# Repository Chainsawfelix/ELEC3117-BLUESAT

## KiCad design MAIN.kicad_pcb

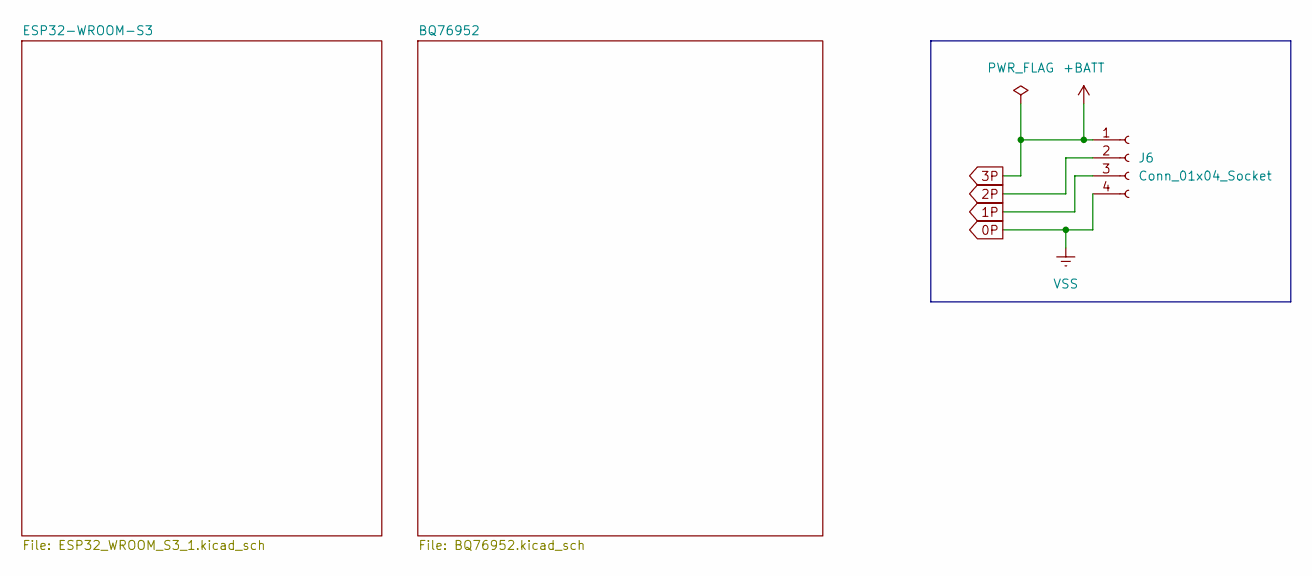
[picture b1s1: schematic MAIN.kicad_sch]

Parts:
J6: Conn_01x04_Socket; JST_XH_B4B-XH-A_1x04_P2.50mm_Vertical

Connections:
0P: J6.4; also elsewhere on the board
1P: J6.3; also elsewhere on the board
2P: J6.2; also elsewhere on the board

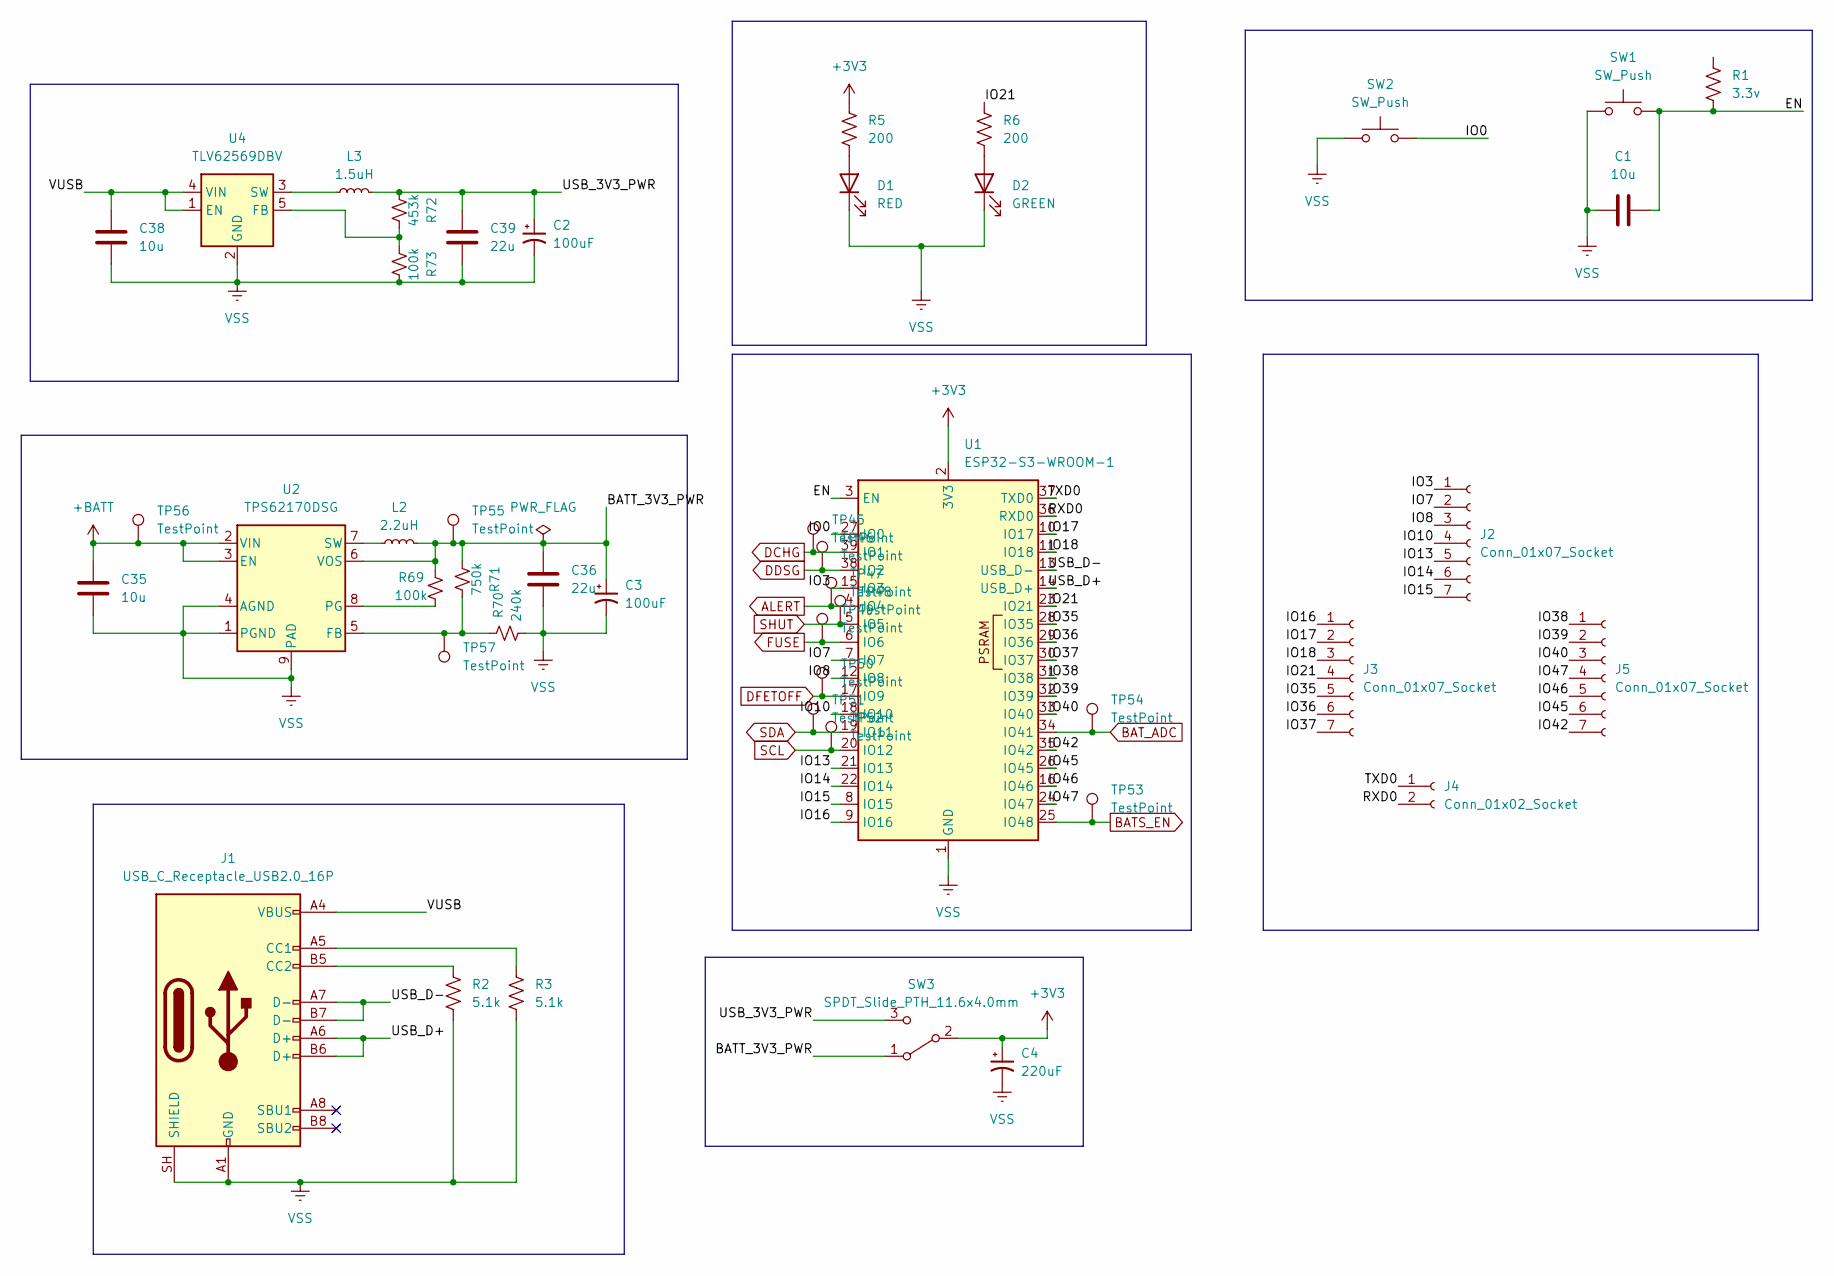
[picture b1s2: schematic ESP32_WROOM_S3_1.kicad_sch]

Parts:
C1, C35, C38: 10u; C_0805_2012Metric
C2, C3: 100uF; CP_Elec_6.3x5.8
C4: 220uF; CP_Elec_6.3x5.8
C36, C39: 22u; C_0805_2012Metric
D1: RED; LED_0805_2012Metric
D2: GREEN; LED_0805_2012Metric
J1: USB_C_Receptacle_USB2.0_16P; USB_C_Receptacle_GCT_USB4105-xx-A_16P_TopMnt_Horizontal
J2, J3, J5: Conn_01x07_Socket; JST_XH_B7B-XH-A_1x07_P2.50mm_Vertical
J4: Conn_01x02_Socket; JST_XH_B2B-XH-A_1x02_P2.50mm_Vertical
L2: 2.2uH; L_Wuerth_MAPI-3020
L3: 1.5uH; L_Wuerth_MAPI-3020
R1: 3.3v; R_0805_2012Metric
R2, R3: 5.1k; R_0805_2012Metric
R5, R6: 200; R_0805_2012Metric
R69, R73: 100k; R_0805_2012Metric
R70: 240k; R_0805_2012Metric
R71: 750k; R_0805_2012Metric
R72: 453k; R_0805_2012Metric
SW1, SW2: SW_Push; Push_SMD_4.2x3.2mm
SW3: SPDT_Slide_PTH_11.6x4.0mm; Slide_SPDT_PTH_11.6x4.0mm
TP45, TP46, TP47, TP48, TP49, TP50, TP51, TP52, TP53, TP54, TP55, TP56, TP57: TestPoint; TestPoint_Pad_D1.0mm
U1: ESP32-S3-WROOM-1
U2: TPS62170DSG; WSON-8-1EP_2x2mm_P0.5mm_EP0.9x1.6mm_ThermalVias
U4: TLV62569DBV; SOT-23-5

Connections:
0P: C1.1, C2.2, C3.2, C4.2, C35.2, C36.2, C38.2, C39.2, D1.1 (K), D2.1 (K), J1.A1 (GND), J1.A12 (GND), J1.B1 (GND), J1.B12 (GND), J1.SH (SHIELD), R2.2, R3.2, R70.2, R73.2, SW1.1, SW2.1, U1.1 (GND), U1.40 (GND), U1.41 (GND), U2.1 (PGND), U2.4 (AGND), U2.9 (PAD), U4.2 (GND); also elsewhere on the board
+3V3: C4.1, R5.1, SW3.2 (B), U1.2 (3V3); also elsewhere on the board
/ESP32-WROOM-S3/BATT_3V3_PWR: C3.1, C36.1, L2.2, R69.1, R71.1, SW3.1 (A), TP55.1 (1_1), U2.6 (VOS)
/ESP32-WROOM-S3/IO0: SW2.2, U1.27 (IO0)
/ESP32-WROOM-S3/IO3: J2.1, U1.15 (IO3)
/ESP32-WROOM-S3/IO7: J2.2, U1.7 (IO7)
/ESP32-WROOM-S3/IO8: J2.3, U1.12 (IO8)
/ESP32-WROOM-S3/IO10: J2.4, U1.18 (IO10)
/ESP32-WROOM-S3/IO13: J2.5, U1.21 (IO13)
/ESP32-WROOM-S3/IO14: J2.6, U1.22 (IO14)
/ESP32-WROOM-S3/IO15: J2.7, U1.8 (IO15)
/ESP32-WROOM-S3/IO16: J3.1, U1.9 (IO16)
/ESP32-WROOM-S3/IO17: J3.2, U1.10 (IO17)
/ESP32-WROOM-S3/IO18: J3.3, U1.11 (IO18)
/ESP32-WROOM-S3/IO21: J3.4, R6.1, U1.23 (IO21)
/ESP32-WROOM-S3/IO35: J3.5, U1.28 (IO35)
/ESP32-WROOM-S3/IO36: J3.6, U1.29 (IO36)
/ESP32-WROOM-S3/IO37: J3.7, U1.30 (IO37)
/ESP32-WROOM-S3/IO38: J5.1, U1.31 (IO38)
/ESP32-WROOM-S3/IO39: J5.2, U1.32 (IO39)
/ESP32-WROOM-S3/IO40: J5.3, U1.33 (IO40)
/ESP32-WROOM-S3/IO42: J5.7, U1.35 (IO42)
/ESP32-WROOM-S3/IO45: J5.6, U1.26 (IO45)
/ESP32-WROOM-S3/IO46: J5.5, U1.16 (IO46)
/ESP32-WROOM-S3/IO47: J5.4, U1.24 (IO47)
/ESP32-WROOM-S3/RXD0: J4.2, U1.36 (RXD0)
/ESP32-WROOM-S3/TXD0: J4.1, U1.37 (TXD0)
/ESP32-WROOM-S3/USB_3V3_PWR: C2.1, C39.1, L3.2, R72.1, SW3.3 (C)
/ESP32-WROOM-S3/USB_D+: J1.A6 (D+), J1.B6 (D+), U1.14 (USB_D+)
/ESP32-WROOM-S3/USB_D-: J1.A7 (D-), J1.B7 (D-), U1.13 (USB_D-)
/ESP32-WROOM-S3/VUSB: C38.1, J1.A4 (VBUS), J1.A9 (VBUS), J1.B4 (VBUS), J1.B9 (VBUS), U4.1 (EN), U4.4 (VIN)
ALERT: TP47.1, U1.4 (IO4); also elsewhere on the board
BATS_EN: TP53.1 (1_1), U1.25 (IO48); also elsewhere on the board
BAT_ADC: TP54.1 (1_1), U1.34 (IO41); also elsewhere on the board
DCHG: TP45.1, U1.39 (IO1); also elsewhere on the board
DDSG: TP46.1, U1.38 (IO2); also elsewhere on the board
DFETOFF: TP50.1, U1.17 (IO9); also elsewhere on the board
FUSE: TP49.1 (1_1), U1.6 (IO6); also elsewhere on the board
unnamed: D1.2 (A), R5.2
unnamed: D2.2 (A), R6.2
unnamed: J1.A5 (CC1), R3.1
unnamed: J1.B5 (CC2), R2.1
unnamed: R70.1, R71.2, TP57.1 (1_1), U2.5 (FB)
unnamed: R69.2, U2.8 (PG)
unnamed: L2.1, U2.7 (SW)
unnamed: R72.2, R73.1, U4.5 (FB)
unnamed: L3.1, U4.3 (SW)
SCL: TP52.1, U1.20 (IO12); also elsewhere on the board
SDA: TP51.1 (1_1), U1.19 (IO11); also elsewhere on the board
SHUT: TP48.1 (1_1), U1.5 (IO5); also elsewhere on the board

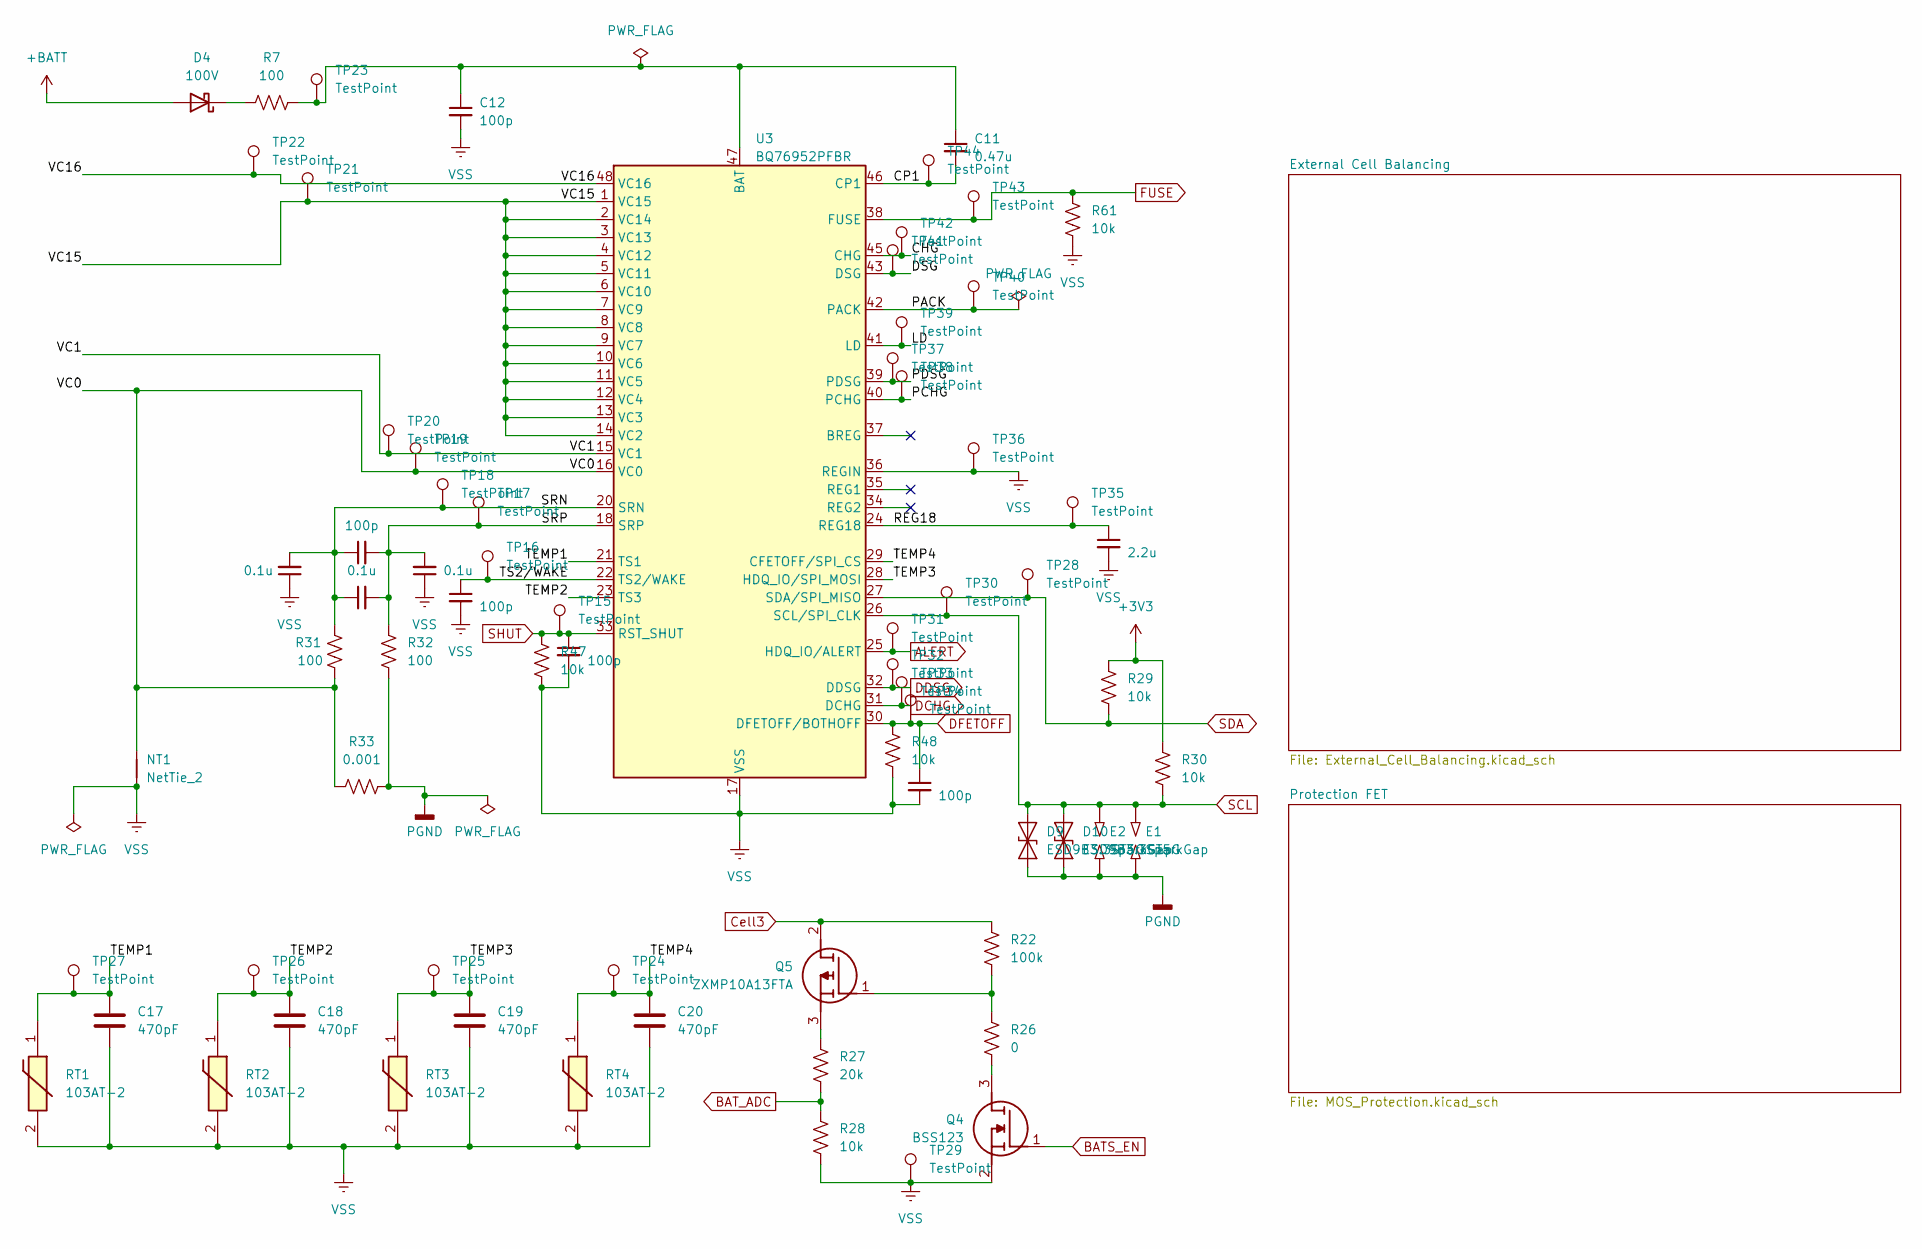
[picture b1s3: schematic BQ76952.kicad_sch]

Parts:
C11: 0.47u; C_0805_2012Metric
C12, C22, C30, C31, C32: 100p; C_0805_2012Metric
C17, C18, C19, C20: 470pF; C_0805_2012Metric
C21: 2.2u; C_0805_2012Metric
C23, C24, C25: 0.1u; C_0805_2012Metric
D4: 100V; D_0805_2012Metric
D9, D10: ESD9B3.3ST5G; D_SOD-923
E1, E2: SparkGap; SolderJumper-2_P1.3mm_Open_TrianglePad1.0x1.5mm
NT1: NetTie_2; SolderJumper-2_P1.3mm_Bridged2Bar_Pad1.0x1.5mm
Q4: BSS123; SOT96P237X111-3N; Mouser Part Number 512-BSS123
Q5: ZXMP10A13FTA; SOT96P240X110-3N; Mouser Part Number 522-ZXMP10A13FTA
R7, R31, R32: 100; R_0805_2012Metric
R22: 100k; R_0805_2012Metric
R26: 0; R_0805_2012Metric
R27: 20k; R_0805_2012Metric
R28, R29, R30, R47, R48, R61: 10k; R_0805_2012Metric
R33: 0.001; R_2512_6332Metric
RT1, RT2, RT3, RT4: 103AT-2; 103AT2; Mouser Part Number 954-103AT-2
TP15, TP16, TP17, TP18, TP19, TP20, TP21, TP22, TP23, TP24, TP25, TP26, TP27, TP28, TP29, TP30, TP31, TP32, TP33, TP34, TP35, TP36, TP37, TP38, TP39, TP40, TP41, TP42, TP43, TP44: TestPoint; TestPoint_Pad_D1.0mm
U3: BQ76952PFBR; TQFP-48_7x7mm_P0.5mm

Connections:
0P: C12.2, C17.2, C18.2, C19.2, C20.2, C21.2, C24.1, C25.1, C30.2, C31.2, C32.2, NT1.1, Q4.2 (S), R28.2, R47.2, R48.2, R61.2, RT1.2, RT2.2, RT3.2, RT4.2, TP29.1 (1_1), TP36.1 (1_1), U3.17 (VSS), U3.36 (REGIN); also elsewhere on the board
+3V3: R29.1, R30.1; also elsewhere on the board
/BQ76952/CHG: TP42.1 (1_1), U3.45 (CHG)
/BQ76952/CP1: C11.2, TP44.1 (1_1), U3.46 (CP1)
/BQ76952/DSG: TP41.1 (1_1), U3.43 (DSG)
/BQ76952/LD: TP39.1 (1_1), U3.41 (LD)
/BQ76952/PACK: TP40.1 (1_1), U3.42 (PACK)
/BQ76952/PCHG: TP38.1 (1_1), U3.40 (PCHG)
/BQ76952/PDSG: TP37.1 (1_1), U3.39 (PDSG)
/BQ76952/REG18: C21.1, TP35.1 (1_1), U3.24 (REG18)
/BQ76952/SRN: C22.1, C23.1, C24.2, R31.1, TP18.1 (1_1), U3.20 (SRN)
/BQ76952/SRP: C22.2, C23.2, C25.2, R32.1, TP17.1 (1_1), U3.18 (SRP)
/BQ76952/TEMP1: C17.1, RT1.1, TP27.1 (1_1), U3.21 (TS1)
/BQ76952/TEMP2: C18.1, RT2.1, TP26.1 (1_1), U3.23 (TS3)
/BQ76952/TEMP3: C19.1, RT3.1, TP25.1 (1_1), U3.28 (HDQ_IO/SPI_MOSI)
/BQ76952/TEMP4: C20.1, RT4.1, TP24.1 (1_1), U3.29 (CFETOFF/SPI_CS)
/BQ76952/TS2/WAKE: C30.1, TP16.1 (1_1), U3.22 (TS2/WAKE)
/BQ76952/VC0: NT1.2, R31.2, R33.1, TP19.1 (1_1), U3.16 (VC0); also elsewhere on the board
/BQ76952/VC1: TP20.1 (1_1), U3.15 (VC1); also elsewhere on the board
/BQ76952/VC15: TP21.1 (1_1), U3.1 (VC15), U3.2 (VC14), U3.3 (VC13), U3.4 (VC12), U3.5 (VC11), U3.6 (VC10), U3.7 (VC9), U3.8 (VC8), U3.9 (VC7), U3.10 (VC6), U3.11 (VC5), U3.12 (VC4), U3.13 (VC3), U3.14 (VC2); also elsewhere on the board
ALERT: TP31.1 (1_1), U3.25 (HDQ_IO/ALERT); also elsewhere on the board
BATS_EN: Q4.1 (G); also elsewhere on the board
BAT_ADC: R27.2, R28.1; also elsewhere on the board
Cell3: Q5.2 (D), R22.1
DCHG: TP33.1 (1_1), U3.31 (DCHG); also elsewhere on the board
DDSG: TP32.1 (1_1), U3.32 (DDSG); also elsewhere on the board
DFETOFF: C32.1, R48.1, TP34.1 (1_1), U3.30 (DFETOFF/BOTHOFF); also elsewhere on the board
FUSE: R61.1, TP43.1 (1_1), U3.38 (FUSE); also elsewhere on the board
unnamed: D4.1 (K), R7.1
unnamed: Q4.3 (D), R26.2
unnamed: Q5.1 (G), R22.2, R26.1
unnamed: Q5.3 (S), R27.1
unnamed 109: C11.1, C12.1, R7.2, TP23.1 (1_1), U3.47 (BAT); also elsewhere on the board
PACK-: D9.1 (A1), D10.1 (A1), E1.1, E2.1, R32.2, R33.2; also elsewhere on the board
SCL: D9.2 (A2), D10.2 (A2), E1.2, E2.2, R30.2, TP30.1 (1_1), U3.26 (SCL/SPI_CLK); also elsewhere on the board
SDA: R29.2, TP28.1 (1_1), U3.27 (SDA/SPI_MISO); also elsewhere on the board
SHUT: C31.1, R47.1, TP15.1 (1_1), U3.33 (RST_SHUT); also elsewhere on the board

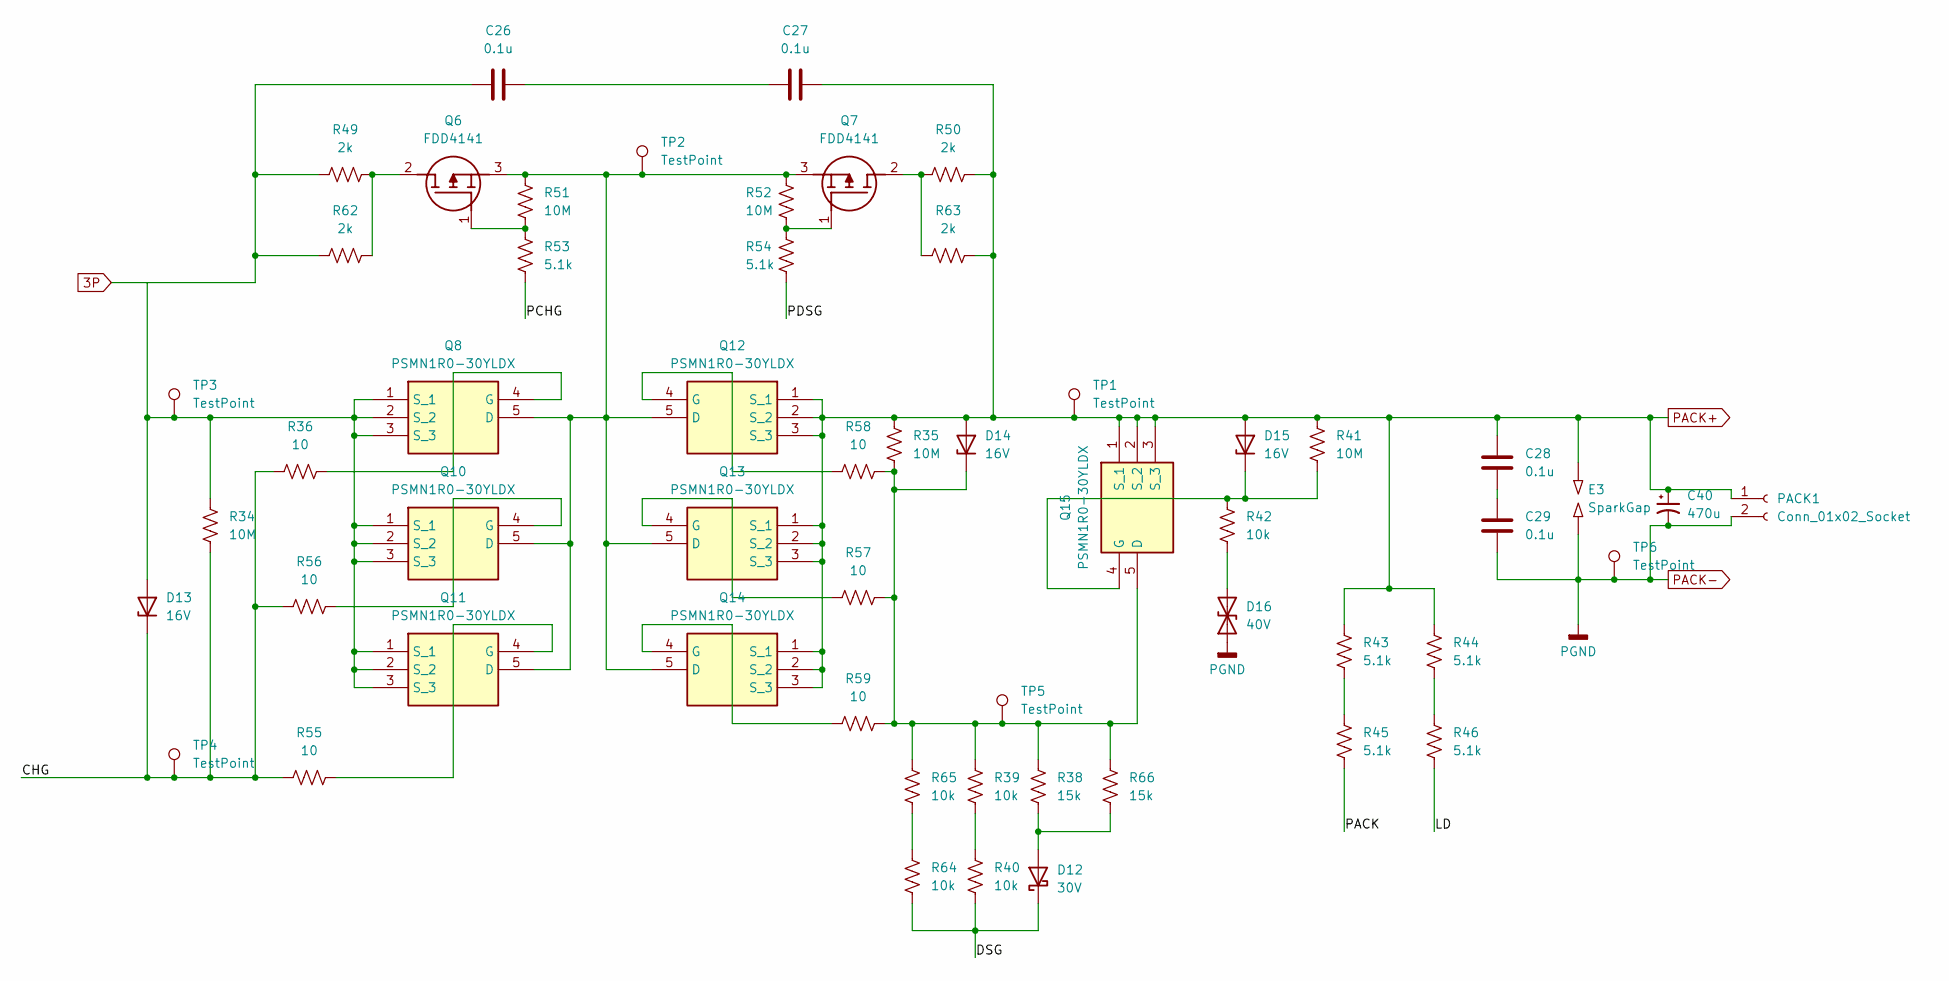
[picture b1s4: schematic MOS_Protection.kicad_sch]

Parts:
C26, C27, C28, C29: 0.1u; C_0805_2012Metric
C40: 470u; C_Elec_8x10.2
D12: 30V; D_SOD-123
D13, D14, D15: 16V; D_SOD-123
D16: 40V; D_SOD-123
E3: SparkGap; SolderJumper-2_P1.3mm_Open_TrianglePad1.0x1.5mm
PACK1: Conn_01x02_Socket; AMASS_XT60-F_1x02_P7.20mm_Vertical
Q6, Q7: FDD4141; FQD1N80TM; Mouser Part Number 512-FDD4141
Q8, Q10, Q11, Q12, Q13, Q14, Q15: PSMN1R0-30YLDX; PSMN5R660YLX; Mouser Part Number 771-PSMN1R0-30YLDX
R34, R35, R41, R51, R52: 10M; R_0805_2012Metric
R36, R55, R56, R57, R58, R59: 10; R_0805_2012Metric
R38, R66: 15k; R_0805_2012Metric
R39, R40, R42, R64, R65: 10k; R_0805_2012Metric
R43, R44, R45, R46, R53, R54: 5.1k; R_0805_2012Metric
R49, R50, R62, R63: 2k; R_0805_2012Metric
TP1, TP2, TP3, TP4, TP5, TP6: TestPoint; TestPoint_Pad_D1.0mm

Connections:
/BQ76952/Protection FET/CHG: D13.1 (K), R34.2, R36.1, R55.1, R56.1, TP4.1
/BQ76952/Protection FET/DSG: D12.1 (K), R40.2, R64.2
/BQ76952/Protection FET/LD: R46.2
/BQ76952/Protection FET/PACK: R45.2
/BQ76952/Protection FET/PCHG: R53.1
/BQ76952/Protection FET/PDSG: R54.1
unnamed: C26.2, C27.1
unnamed: C28.1, C29.2
unnamed: D12.2 (A), R38.2, R66.2
unnamed: D13.2 (A), Q8.1 (S_1), Q8.2 (S_2), Q8.3 (S_3), Q10.1 (S_1), Q10.2 (S_2), Q10.3 (S_3), Q11.1 (S_1), Q11.2 (S_2), Q11.3 (S_3), R34.1, TP3.1
unnamed: D14.1 (K), Q15.5 (D), Q15.6, R35.2, R38.1, R39.1, R57.2, R58.2, R59.2, R65.1, R66.1, TP5.1 (1_1)
unnamed: D15.1 (K), Q15.4 (G), R41.2, R42.1
unnamed: D16.2 (A2), R42.2
unnamed: Q6.2 (D), R49.2, R62.2
unnamed: Q6.1 (G), R51.1, R53.2
unnamed: Q7.2 (D), R50.1, R63.1
unnamed: Q7.1 (G), R52.1, R54.2
unnamed: Q8.4 (G), R36.2
unnamed: Q6.3 (S), Q7.3 (S), Q8.5 (D), Q8.6, Q10.5 (D), Q10.6, Q11.5 (D), Q11.6, Q12.5 (D), Q12.6, Q13.5 (D), Q13.6, Q14.5 (D), Q14.6, R51.2, R52.2, TP2.1 (1_1)
unnamed: Q10.4 (G), R56.2
unnamed: Q11.4 (G), R55.2
unnamed: Q12.4 (G), R58.1
unnamed: Q13.4 (G), R57.1
unnamed: Q14.4 (G), R59.1
unnamed: R39.2, R40.1
unnamed: R43.2, R45.1
unnamed: R44.2, R46.1
unnamed: R64.1, R65.2
PACK+: C27.2, C28.2, C40.1, D14.2 (A), D15.2 (A), E3.2, PACK1.1, Q12.1 (S_1), Q12.2 (S_2), Q12.3 (S_3), Q13.1 (S_1), Q13.2 (S_2), Q13.3 (S_3), Q14.1 (S_1), Q14.2 (S_2), Q14.3 (S_3), Q15.1 (S_1), Q15.2 (S_2), Q15.3 (S_3), R35.1, R41.1, R43.1, R44.1, R50.2, R63.2, TP1.1
PACK-: C29.1, C40.2, D16.1 (A1), E3.1, PACK1.2, TP6.1; also elsewhere on the board

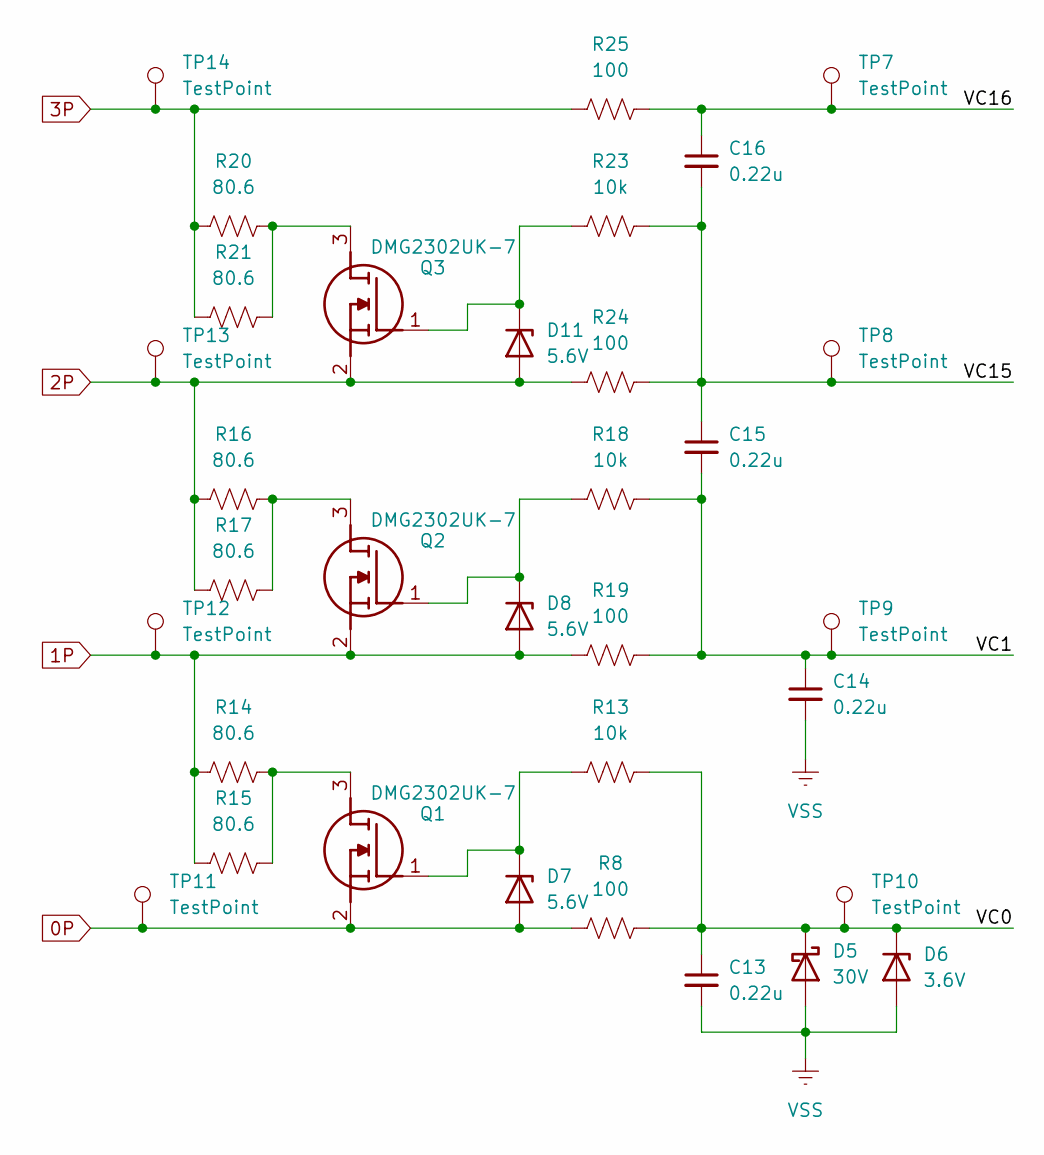
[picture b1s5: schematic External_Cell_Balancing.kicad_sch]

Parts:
C13, C14, C15, C16: 0.22u; C_0805_2012Metric
D5: 30V; D_SOD-123
D6: 3.6V; D_SOD-123
D7, D8, D11: 5.6V; D_SOD-123
Q1, Q2, Q3: DMG2302UK-7; SOT96P240X110-3N; Mouser Part Number 621-DMG2302UK-7
R8, R19, R24, R25: 100; R_0805_2012Metric
R13, R18, R23: 10k; R_0805_2012Metric
R14, R15, R16, R17, R20, R21: 80.6; R_0805_2012Metric
TP7, TP8, TP9, TP10, TP11, TP12, TP13, TP14: TestPoint; TestPoint_Pad_D1.0mm

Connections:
0P: C13.2, C14.2, D5.2 (A), D6.2 (A), D7.2 (A), Q1.2 (S), R8.2, TP11.1 (1_1); also elsewhere on the board
1P: D8.2 (A), Q2.2 (S), R14.1, R15.1, R19.2, TP12.1 (1_1); also elsewhere on the board
2P: D11.2 (A), Q3.2 (S), R16.1, R17.1, R24.2, TP13.1 (1_1); also elsewhere on the board
/BQ76952/External Cell Balancing/VC0: C13.1, D5.1 (K), D6.1 (K), R8.1, R13.1, TP10.1 (1_1)
/BQ76952/External Cell Balancing/VC1: C14.1, C15.2, R18.1, R19.1, TP9.1 (1_1)
/BQ76952/External Cell Balancing/VC15: C15.1, C16.2, R23.1, R24.1, TP8.1 (1_1)
/BQ76952/External Cell Balancing/VC16: C16.1, R25.1, TP7.1 (1_1)
unnamed: D7.1 (K), Q1.1 (G), R13.2
unnamed: D8.1 (K), Q2.1 (G), R18.2
unnamed: D11.1 (K), Q3.1 (G), R23.2
unnamed: Q1.3 (D), R14.2, R15.2
unnamed: Q2.3 (D), R16.2, R17.2
unnamed: Q3.3 (D), R20.2, R21.2

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
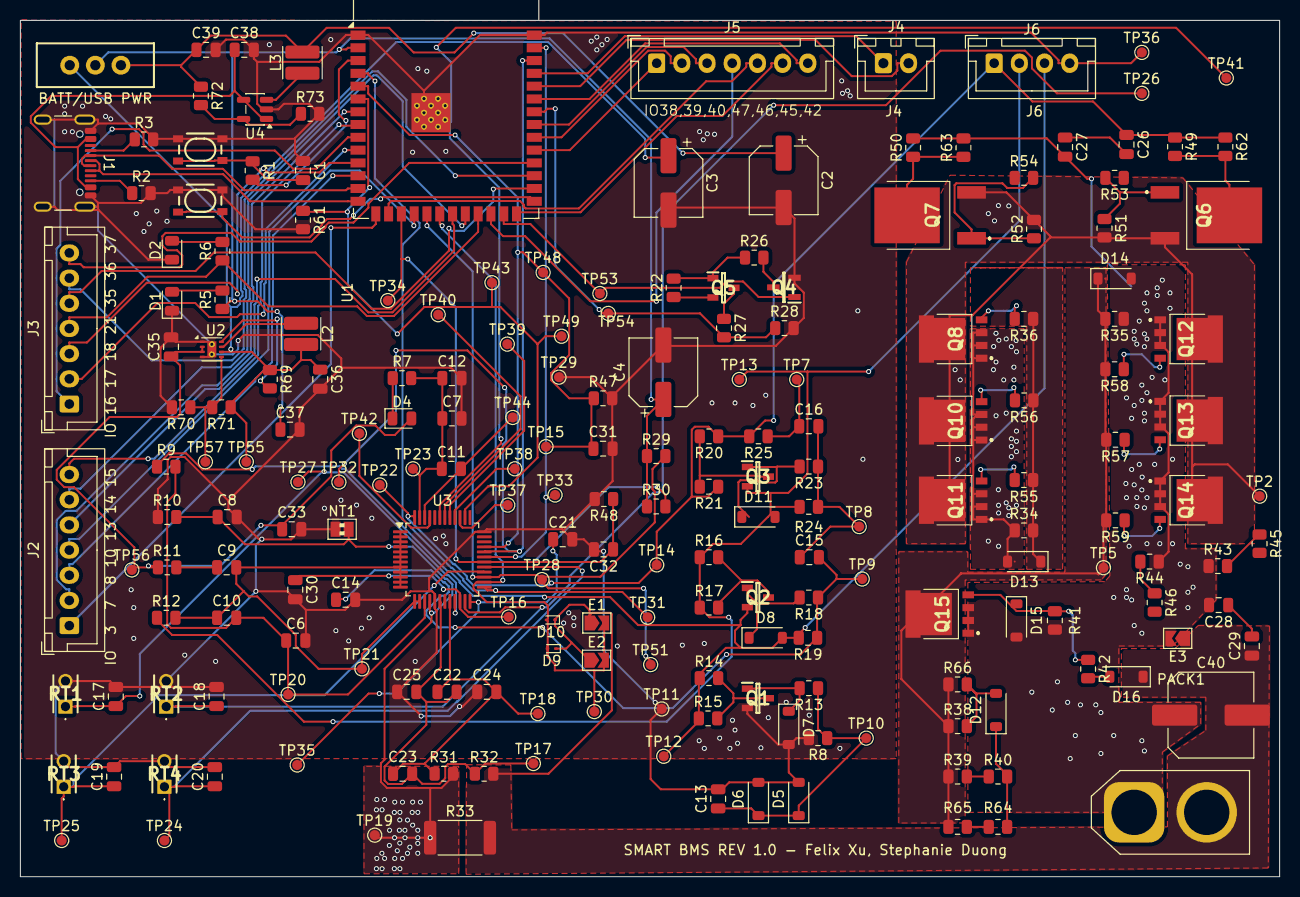
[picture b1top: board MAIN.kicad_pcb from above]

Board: 2 copper layers, 125.0 x 85.0 mm, 207 parts (0 on the bottom side), 116 nets.

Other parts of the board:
C6, C8, C9, C10: 0.22u; C_0805_2012Metric
C7, C33: NC; C_0805_2012Metric
C37: 100u; C_0805_2012Metric
R9, R10, R11, R12: 20; R_0805_2012Metric

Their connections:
0P: C6.2, C7.2, C8.2, C33.2, C37.2, R10.1; also elsewhere on the board
1P: R9.1; also elsewhere on the board
2P: R12.1; also elsewhere on the board
+3V3: C37.1; also elsewhere on the board
/BQ76952/VC0: C8.1, R10.2; also elsewhere on the board
/BQ76952/VC1: C6.1, C10.2, R9.2; also elsewhere on the board
/BQ76952/VC15: C9.2, C10.1, R12.2; also elsewhere on the board
/BQ76952/VC16: C9.1, R11.2
unnamed 109: C7.1; also elsewhere on the board

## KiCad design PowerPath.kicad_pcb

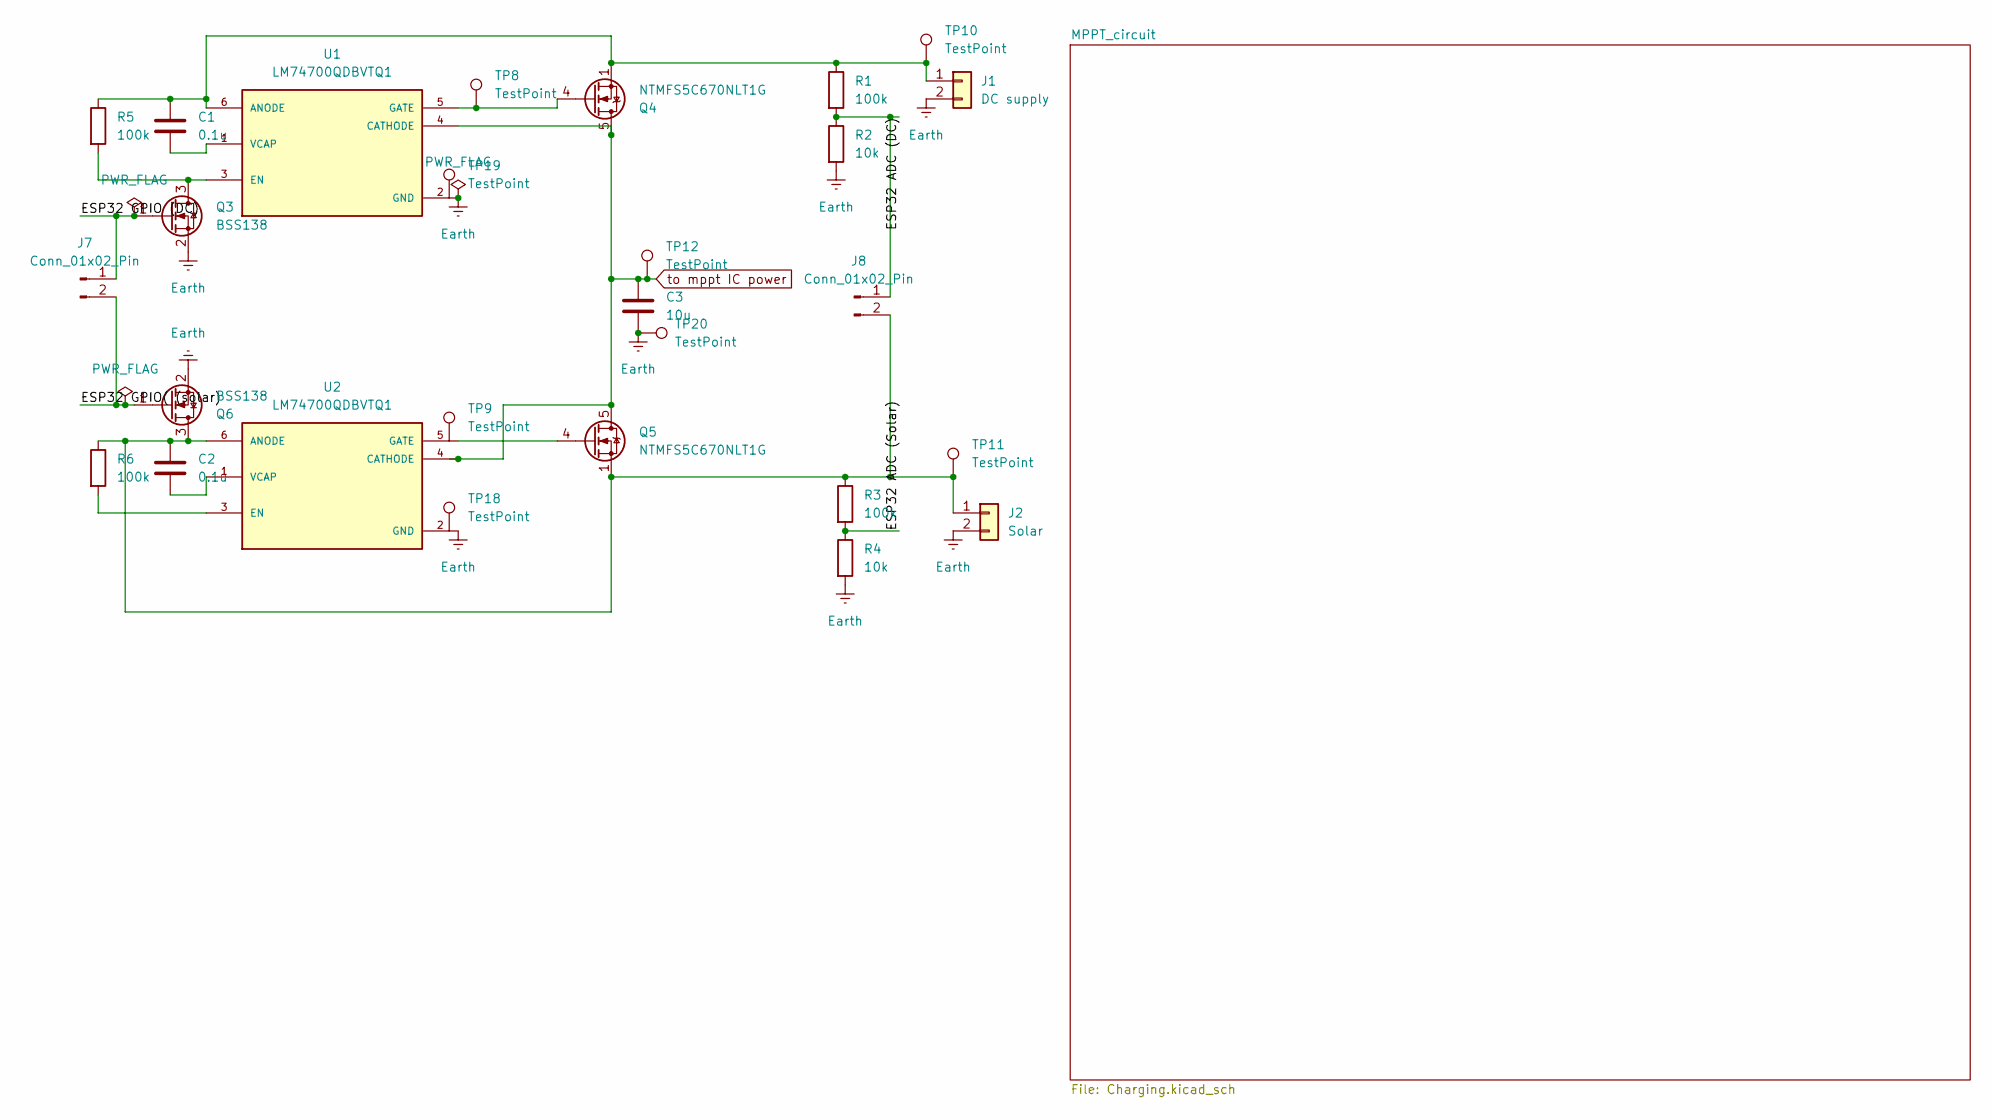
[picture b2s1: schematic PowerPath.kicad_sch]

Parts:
C1, C2: 0.1u; C_0805_2012Metric_Pad1.18x1.45mm_HandSolder
C3: 10u; C_1206_3216Metric_Pad1.33x1.80mm_HandSolder
J1: DC supply; XT60_Pigtail_14AWG
J2: Solar; XT60_Pigtail_14AWG
J7, J8: Conn_01x02_Pin; JST_XH_B2B-XH-A_1x02_P2.50mm_Vertical
Q3, Q6: BSS138; SOT-23
Q4, Q5: NTMFS5C670NLT1G; ONSemi_SO-8FL_488AA
R1, R3, R5, R6: 100k; R_0805_2012Metric_Pad1.20x1.40mm_HandSolder
R2, R4: 10k; R_0805_2012Metric_Pad1.20x1.40mm_HandSolder
TP8, TP9, TP10, TP11, TP12: TestPoint; TestPoint_Pad_D1.0mm
TP18, TP19, TP20: TestPoint; TestPoint_Loop_D2.50mm_Drill1.0mm
U1, U2: LM74700QDBVTQ1; SOT-23-6_Handsoldering; PARTREV F

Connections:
/ESP32 ADC (DC): J8.1, R1.2, R2.1
/ESP32 ADC (Solar): R3.2, R4.1
/ESP32 GPIO (DC): J7.1, Q3.1 (G)
/ESP32 GPIO( (solar): J7.2, Q6.1 (G)
Earth: C3.2, J1.2, J2.2, Q3.2 (S), Q6.2 (S), R2.2, R4.2, TP18.1 (1_1), TP19.1 (1_1), TP20.1 (1_1), U1.2 (GND), U2.2 (GND); also elsewhere on the board
unnamed: C1.1, J1.1, Q4.1 (S), Q4.2 (S), Q4.3 (S), R1.1, R5.1, TP10.1 (1_1), U1.6 (ANODE)
unnamed: C2.1, J2.1, J8.2, Q5.1 (S), Q5.2 (S), Q5.3 (S), Q6.3 (D), R3.1, R6.1, TP11.1 (1_1), U2.6 (ANODE)
unnamed: Q3.3 (D), R5.2, U1.3 (EN)
unnamed: Q4.4 (G), TP8.1 (1_1), U1.5 (GATE)
unnamed: C1.2, U1.1 (VCAP)
unnamed: R6.2, U2.3 (EN)
unnamed: C2.2, U2.1 (VCAP)
to mppt IC power: C3.1, Q4.5 (D), Q5.5 (D), TP12.1 (1_1), U1.4 (CATHODE), U2.4 (CATHODE); also elsewhere on the board
